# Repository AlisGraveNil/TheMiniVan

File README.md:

# The MiniVan
 A 100% in 3 Parts

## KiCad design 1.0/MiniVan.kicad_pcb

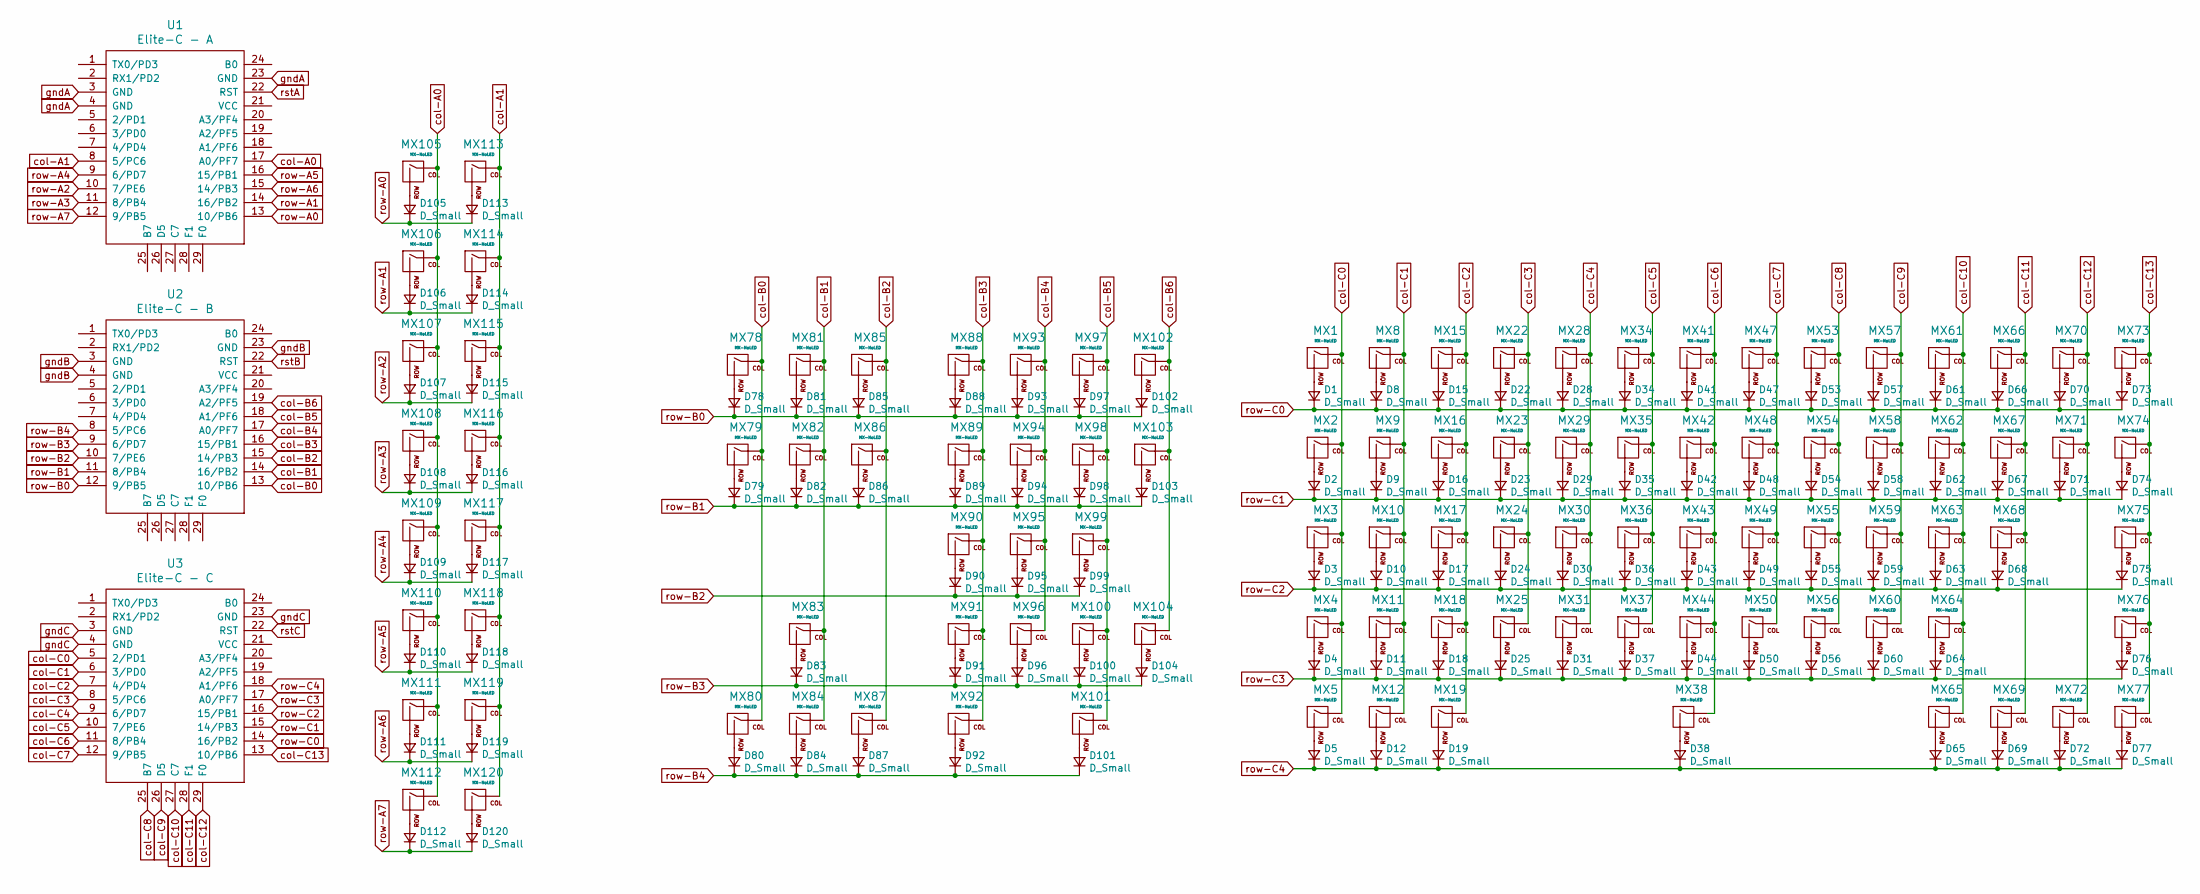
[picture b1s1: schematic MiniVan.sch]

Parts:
D1, D2, D3, D4, D5, D8, D9, D10, D11, D12, D15, D16, D17, D18, D19, D22, D23, D24, D25, D28, D29, D30, D31, D34, D35, D36, D37, D38, D41, D42, D43, D44, D47, D48, D49, D50, D53, D54, D55, D56, D57, D58, D59, D60, D61, D62, D63, D64, D65, D66, D67, D68, D69, D70, D71, D72, D73, D74, D75, D76, D77, D78, D79, D80, D81, D82, D83, D84, D85, D86, D87, D88, D89, D90, D91, D92, D93, D94, D95, D96, D97, D98, D99, D100, D101, D102, D103, D104, D105, D106, D107, D108, D109, D110, D111, D112, D113, D114, D115, D116, D117, D118, D119, D120: D_Small; D_DO-35_SOD27_P3.81mm_Vertical_AnodeUp
MX1, MX8, MX9, MX10, MX11, MX15, MX16, MX17, MX18, MX22, MX23, MX24, MX25, MX28, MX29, MX30, MX31, MX34, MX35, MX36, MX37, MX41, MX42, MX43, MX44, MX47, MX48, MX49, MX50, MX53, MX54, MX55, MX56, MX57, MX58, MX59, MX60, MX61, MX62, MX63, MX64, MX66, MX67, MX68, MX70, MX71, MX78, MX79, MX80, MX81, MX82, MX83, MX84, MX85, MX86, MX87, MX88, MX89, MX90, MX91, MX93, MX94, MX95, MX96, MX97, MX98, MX99, MX100, MX101, MX102, MX105, MX106, MX107, MX108, MX109, MX110, MX111, MX112, MX113, MX114, MX115, MX116, MX117, MX118, MX119, MX120: MX-NoLED; MX-1U-NoLED
MX2, MX74: MX-NoLED; MX-1.5U-NoLED
MX3: MX-NoLED; MX-1.75U-NoLED
MX4, MX75: MX-NoLED; MX-2.25U-NoLED
MX5, MX12, MX19, MX65, MX69, MX72, MX77: MX-NoLED; MX-1.25U-NoLED
MX38: MX-NoLED; MX-6.25U-NoLED
MX73, MX92, MX103, MX104: MX-NoLED; MX-2U-NoLED
MX76: MX-NoLED; MX-2.75U-NoLED
U1: Elite-C - A; Elite-C-castellated-29pin-holes
U2: Elite-C - B; Elite-C-castellated-29pin-holes
U3: Elite-C - C; Elite-C-castellated-29pin-holes

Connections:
unnamed: D1.2 (A), MX1.2 (ROW)
unnamed: D2.2 (A), MX2.2 (ROW)
unnamed: D3.2 (A), MX3.2 (ROW)
unnamed: D4.2 (A), MX4.2 (ROW)
unnamed: D5.2 (A), MX5.2 (ROW)
unnamed: D8.2 (A), MX8.2 (ROW)
unnamed: D9.2 (A), MX9.2 (ROW)
unnamed: D10.2 (A), MX10.2 (ROW)
unnamed: D11.2 (A), MX11.2 (ROW)
unnamed: D12.2 (A), MX12.2 (ROW)
unnamed: D15.2 (A), MX15.2 (ROW)
unnamed: D16.2 (A), MX16.2 (ROW)
unnamed: D17.2 (A), MX17.2 (ROW)
unnamed: D18.2 (A), MX18.2 (ROW)
unnamed: D19.2 (A), MX19.2 (ROW)
unnamed: D22.2 (A), MX22.2 (ROW)
unnamed: D23.2 (A), MX23.2 (ROW)
unnamed: D24.2 (A), MX24.2 (ROW)
unnamed: D25.2 (A), MX25.2 (ROW)
unnamed: D28.2 (A), MX28.2 (ROW)
unnamed: D29.2 (A), MX29.2 (ROW)
unnamed: D30.2 (A), MX30.2 (ROW)
unnamed: D31.2 (A), MX31.2 (ROW)
unnamed: D34.2 (A), MX34.2 (ROW)
unnamed: D35.2 (A), MX35.2 (ROW)
unnamed: D36.2 (A), MX36.2 (ROW)
unnamed: D37.2 (A), MX37.2 (ROW)
unnamed: D38.2 (A), MX38.2 (ROW)
unnamed: D41.2 (A), MX41.2 (ROW)
unnamed: D42.2 (A), MX42.2 (ROW)
unnamed: D43.2 (A), MX43.2 (ROW)
unnamed: D44.2 (A), MX44.2 (ROW)
unnamed: D47.2 (A), MX47.2 (ROW)
unnamed: D48.2 (A), MX48.2 (ROW)
unnamed: D49.2 (A), MX49.2 (ROW)
unnamed: D50.2 (A), MX50.2 (ROW)
unnamed: D53.2 (A), MX53.2 (ROW)
unnamed: D54.2 (A), MX54.2 (ROW)
unnamed: D55.2 (A), MX55.2 (ROW)
unnamed: D56.2 (A), MX56.2 (ROW)
unnamed: D57.2 (A), MX57.2 (ROW)
unnamed: D58.2 (A), MX58.2 (ROW)
unnamed: D59.2 (A), MX59.2 (ROW)
unnamed: D60.2 (A), MX60.2 (ROW)
unnamed: D61.2 (A), MX61.2 (ROW)
unnamed: D62.2 (A), MX62.2 (ROW)
unnamed: D63.2 (A), MX63.2 (ROW)
unnamed: D64.2 (A), MX64.2 (ROW)
unnamed: D65.2 (A), MX65.2 (ROW)
unnamed: D66.2 (A), MX66.2 (ROW)
unnamed: D67.2 (A), MX67.2 (ROW)
unnamed: D68.2 (A), MX68.2 (ROW)
unnamed: D69.2 (A), MX69.2 (ROW)
unnamed: D70.2 (A), MX70.2 (ROW)
unnamed: D71.2 (A), MX71.2 (ROW)
unnamed: D72.2 (A), MX72.2 (ROW)
unnamed: D73.2 (A), MX73.2 (ROW)
unnamed: D74.2 (A), MX74.2 (ROW)
unnamed: D75.2 (A), MX75.2 (ROW)
unnamed: D76.2 (A), MX76.2 (ROW)
unnamed: D77.2 (A), MX77.2 (ROW)
unnamed: D78.2 (A), MX78.2 (ROW)
unnamed: D79.2 (A), MX79.2 (ROW)
unnamed: D80.2 (A), MX80.2 (ROW)
unnamed: D81.2 (A), MX81.2 (ROW)
unnamed: D82.2 (A), MX82.2 (ROW)
unnamed: D83.2 (A), MX83.2 (ROW)
unnamed: D84.2 (A), MX84.2 (ROW)
unnamed: D85.2 (A), MX85.2 (ROW)
unnamed: D86.2 (A), MX86.2 (ROW)
unnamed: D87.2 (A), MX87.2 (ROW)
unnamed: D88.2 (A), MX88.2 (ROW)
unnamed: D89.2 (A), MX89.2 (ROW)
unnamed: D90.2 (A), MX90.2 (ROW)
unnamed: D91.2 (A), MX91.2 (ROW)
unnamed: D92.2 (A), MX92.2 (ROW)
unnamed: D93.2 (A), MX93.2 (ROW)
unnamed: D94.2 (A), MX94.2 (ROW)
unnamed: D95.2 (A), MX95.2 (ROW)
unnamed: D96.2 (A), MX96.2 (ROW)
unnamed: D97.2 (A), MX97.2 (ROW)
unnamed: D98.2 (A), MX98.2 (ROW)
unnamed: D99.2 (A), MX99.2 (ROW)
unnamed: D100.2 (A), MX100.2 (ROW)
unnamed: D101.2 (A), MX101.2 (ROW)
unnamed: D102.2 (A), MX102.2 (ROW)
unnamed: D103.2 (A), MX103.2 (ROW)
unnamed: D104.2 (A), MX104.2 (ROW)
unnamed: D105.2 (A), MX105.2 (ROW)
unnamed: D106.2 (A), MX106.2 (ROW)
unnamed: D107.2 (A), MX107.2 (ROW)
unnamed: D108.2 (A), MX108.2 (ROW)
unnamed: D109.2 (A), MX109.2 (ROW)
unnamed: D110.2 (A), MX110.2 (ROW)
unnamed: D111.2 (A), MX111.2 (ROW)
unnamed: D112.2 (A), MX112.2 (ROW)
unnamed: D113.2 (A), MX113.2 (ROW)
unnamed: D114.2 (A), MX114.2 (ROW)
unnamed: D115.2 (A), MX115.2 (ROW)
unnamed: D116.2 (A), MX116.2 (ROW)
unnamed: D117.2 (A), MX117.2 (ROW)
unnamed: D118.2 (A), MX118.2 (ROW)
unnamed: D119.2 (A), MX119.2 (ROW)
unnamed: D120.2 (A), MX120.2 (ROW)
col-A0: MX105.1 (COL), MX106.1 (COL), MX107.1 (COL), MX108.1 (COL), MX109.1 (COL), MX110.1 (COL), MX111.1 (COL), MX112.1 (COL), U1.17 (A0/PF7)
col-A1: MX113.1 (COL), MX114.1 (COL), MX115.1 (COL), MX116.1 (COL), MX117.1 (COL), MX118.1 (COL), MX119.1 (COL), MX120.1 (COL), U1.8 (5/PC6)
col-B0: MX78.1 (COL), MX79.1 (COL), MX80.1 (COL), U2.13 (10/PB6)
col-B1: MX81.1 (COL), MX82.1 (COL), MX83.1 (COL), MX84.1 (COL), U2.14 (16/PB2)
col-B2: MX85.1 (COL), MX86.1 (COL), MX87.1 (COL), U2.15 (14/PB3)
col-B3: MX88.1 (COL), MX89.1 (COL), MX90.1 (COL), MX91.1 (COL), MX92.1 (COL), U2.16 (15/PB1)
col-B4: MX93.1 (COL), MX94.1 (COL), MX95.1 (COL), MX96.1 (COL), U2.17 (A0/PF7)
col-B5: MX97.1 (COL), MX98.1 (COL), MX99.1 (COL), MX100.1 (COL), MX101.1 (COL), U2.18 (A1/PF6)
col-B6: MX102.1 (COL), MX103.1 (COL), MX104.1 (COL), U2.19 (A2/PF5)
col-C0: MX1.1 (COL), MX2.1 (COL), MX3.1 (COL), MX4.1 (COL), MX5.1 (COL), U3.5 (2/PD1)
col-C1: MX8.1 (COL), MX9.1 (COL), MX10.1 (COL), MX11.1 (COL), MX12.1 (COL), U3.6 (3/PD0)
col-C2: MX15.1 (COL), MX16.1 (COL), MX17.1 (COL), MX18.1 (COL), MX19.1 (COL), U3.7 (4/PD4)
col-C3: MX22.1 (COL), MX23.1 (COL), MX24.1 (COL), MX25.1 (COL), U3.8 (5/PC6)
col-C4: MX28.1 (COL), MX29.1 (COL), MX30.1 (COL), MX31.1 (COL), U3.9 (6/PD7)
col-C5: MX34.1 (COL), MX35.1 (COL), MX36.1 (COL), MX37.1 (COL), U3.10 (7/PE6)
col-C6: MX38.1 (COL), MX41.1 (COL), MX42.1 (COL), MX43.1 (COL), MX44.1 (COL), U3.11 (8/PB4)
col-C7: MX47.1 (COL), MX48.1 (COL), MX49.1 (COL), MX50.1 (COL), U3.12 (9/PB5)
col-C8: MX53.1 (COL), MX54.1 (COL), MX55.1 (COL), MX56.1 (COL), U3.25 (B7)
col-C9: MX57.1 (COL), MX58.1 (COL), MX59.1 (COL), MX60.1 (COL), U3.26 (D5)
col-C10: MX61.1 (COL), MX62.1 (COL), MX63.1 (COL), MX64.1 (COL), MX65.1 (COL), U3.27 (C7)
col-C11: MX66.1 (COL), MX67.1 (COL), MX68.1 (COL), MX69.1 (COL), U3.28 (F1)
col-C12: MX70.1 (COL), MX71.1 (COL), MX72.1 (COL), U3.29 (F0)
col-C13: MX73.1 (COL), MX74.1 (COL), MX75.1 (COL), MX76.1 (COL), MX77.1 (COL), U3.13 (10/PB6)
gndA: U1.3 (GND), U1.4 (GND), U1.23 (GND)
gndB: U2.3 (GND), U2.4 (GND), U2.23 (GND)
gndC: U3.3 (GND), U3.4 (GND), U3.23 (GND)
row-A0: D105.1 (K), D113.1 (K), U1.13 (10/PB6)
row-A1: D106.1 (K), D114.1 (K), U1.14 (16/PB2)
row-A2: D107.1 (K), D115.1 (K), U1.10 (7/PE6)
row-A3: D108.1 (K), D116.1 (K), U1.11 (8/PB4)
row-A4: D109.1 (K), D117.1 (K), U1.9 (6/PD7)
row-A5: D110.1 (K), D118.1 (K), U1.16 (15/PB1)
row-A6: D111.1 (K), D119.1 (K), U1.15 (14/PB3)
row-A7: D112.1 (K), D120.1 (K), U1.12 (9/PB5)
row-B0: D78.1 (K), D81.1 (K), D85.1 (K), D88.1 (K), D93.1 (K), D97.1 (K), D102.1 (K), U2.12 (9/PB5)
row-B1: D79.1 (K), D82.1 (K), D86.1 (K), D89.1 (K), D94.1 (K), D98.1 (K), D103.1 (K), U2.11 (8/PB4)
row-B2: D90.1 (K), D95.1 (K), D99.1 (K), U2.10 (7/PE6)
row-B3: D83.1 (K), D91.1 (K), D96.1 (K), D100.1 (K), D104.1 (K), U2.9 (6/PD7)
row-B4: D80.1 (K), D84.1 (K), D87.1 (K), D92.1 (K), D101.1 (K), U2.8 (5/PC6)
row-C0: D1.1 (K), D8.1 (K), D15.1 (K), D22.1 (K), D28.1 (K), D34.1 (K), D41.1 (K), D47.1 (K), D53.1 (K), D57.1 (K), D61.1 (K), D66.1 (K), D70.1 (K), D73.1 (K), U3.14 (16/PB2)
row-C1: D2.1 (K), D9.1 (K), D16.1 (K), D23.1 (K), D29.1 (K), D35.1 (K), D42.1 (K), D48.1 (K), D54.1 (K), D58.1 (K), D62.1 (K), D67.1 (K), D71.1 (K), D74.1 (K), U3.15 (14/PB3)
row-C2: D3.1 (K), D10.1 (K), D17.1 (K), D24.1 (K), D30.1 (K), D36.1 (K), D43.1 (K), D49.1 (K), D55.1 (K), D59.1 (K), D63.1 (K), D68.1 (K), D75.1 (K), U3.16 (15/PB1)
row-C3: D4.1 (K), D11.1 (K), D18.1 (K), D25.1 (K), D31.1 (K), D37.1 (K), D44.1 (K), D50.1 (K), D56.1 (K), D60.1 (K), D64.1 (K), D76.1 (K), U3.17 (A0/PF7)
row-C4: D5.1 (K), D12.1 (K), D19.1 (K), D38.1 (K), D65.1 (K), D69.1 (K), D72.1 (K), D77.1 (K), U3.18 (A1/PF6)
rstA: U1.22 (RST)
rstB: U2.22 (RST)
rstC: U3.22 (RST)

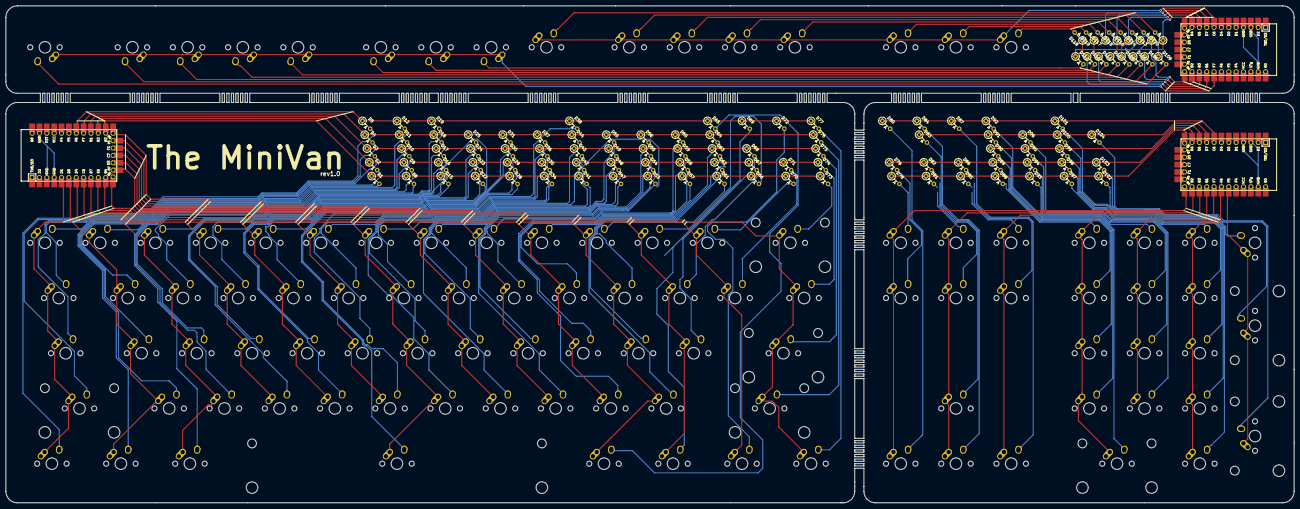
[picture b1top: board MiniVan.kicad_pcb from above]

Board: 2 copper layers, 444.5 x 171.4 mm, 211 parts (0 on the bottom side), 148 nets.

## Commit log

2020-04-28 4/28/20 v2
2020-04-28 4/28/20 v3
2020-04-29 4/28/20 v4
2020-04-30 4/30/20 v1
2020-05-02 5/1/20 v1
2020-05-04 5/4/20 v1
